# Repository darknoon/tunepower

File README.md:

tunepower
=========

TunePower is a simple accessory for [Airport Express](https://www.apple.com/airport-express/) that automatically senses audio and turns on an accessory, namely an audio power amplifier. It is implemented with a [Digispark](http://digistump.com/products/1) microcontroller development board and a [PowerSwitch Tail II](http://www.powerswitchtail.com/Pages/default.aspx) relay to switch AC line voltage, as well as a small backpack board for the Digispark.

This system uses a simple LM741 op-amp circuit to amplify the audio for input into the [ATTiny85](http://www.atmel.com/devices/attiny85.aspx) microcontroller. The microcontroller manages turning on the relay circuit once an audio signal is detected. The software keeps the output on for a period of at least 10 minutes, to avoid rapid cycling of power amplifier.

Future enhancements:
One future feature that could increase reliability is to implement software such that when the circuit shuts off, a lockout period of 1 second is enforced. This will make sure any transients introduced in an AC line voltage transition do not reactivate the detector.

Pictures below:
1. Original prototype under development.
2. Digispark + backpack front view.
3. Digispark + backpack back view.

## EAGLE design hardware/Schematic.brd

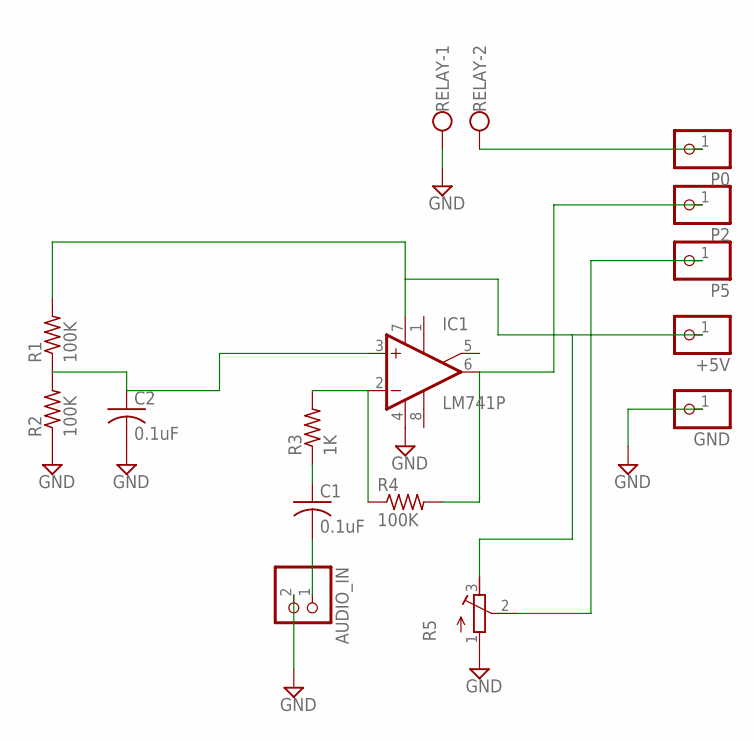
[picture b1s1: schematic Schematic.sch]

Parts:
+5V: PINHD-1X1; 1X01
AUDIO_IN: PINHD-1X2; 1X02
C1, C2: 0.1uF; C025-024X044
GND: PINHD-1X1; 1X01
IC1: LM741P; DIL08
P0, P2, P5: PINHD-1X1; 1X01
R1, R2, R4: 100K; 0207/2V
R3: 1K; 0207/2V
R5: R-TRIMM64W; RTRIM64W
RELAY: W237-102

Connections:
GND: AUDIO_IN.2, C2.2, GND.1, IC1.4 (V-), R2.1, R5.1 (E), RELAY.1
unnamed: C1.1, R3.1
unnamed: C2.1, IC1.3 (+IN), R1.1, R2.2
unnamed: AUDIO_IN.1, C1.2
unnamed: IC1.2 (-IN), R3.2, R4.1
unnamed: IC1.6 (OUT), P2.1, R4.2
unnamed: +5V.1, IC1.7 (V+), R1.2, R5.3 (A)
unnamed: P0.1, RELAY.2
unnamed: P5.1, R5.2 (S)

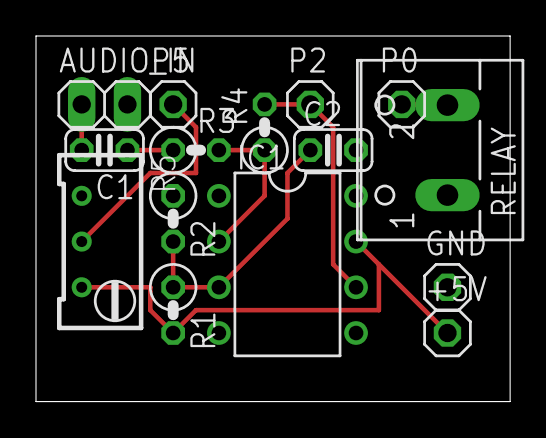
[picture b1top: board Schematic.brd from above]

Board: 2 copper layers, 26.3 x 20.3 mm, 15 parts (0 on the bottom side), 9 nets.

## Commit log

2014-04-07 Add micro controller software v0
2014-04-07 Adding Eagle schematic and board documents for Digispark backpack.
2014-04-07 Adding readme describing the project, as well as images.
2014-04-07 Adding schematic to readme.
2014-04-07 Readme markdown formatting changes and adding a link to ATTiny85.
2014-04-27 Updating readme.
2014-05-05 Updated readme with installed picture.
